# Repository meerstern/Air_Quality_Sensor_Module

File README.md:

# エアクオリティセンサ基板  
Air_Quality_Sensor_Module

## 概要 
  * ルネサスエレクトロニクス製 [室内空気質（IAQ）センサZMOD4410][1]及び[温湿度センサHS3001][2]を搭載したセンサ基板と専用変換基板です  
  * 専用変換基板を使用することで抵抗値からCO2等に変換する計算アルゴリズムをマイコン側に実装する必要がありません  
  * Arduino等のI2C通信を介して専用変換基板から容易に温湿度、CO2値等の情報を読み出すことが可能です 
  * 変換基板の[SEN]のコネクタにセンサ基板を接続し、[MPU]のコネクタにArduino等のマスタデバイスを接続してください  
  * 計算アルゴリズムはメーカ提供の学習済みニューラルネットワークを使用したファームウェア(20/10/19リリース版)を使用しています  
  * 学習済みニューラルネットワークによって従来よりもより正確にCO2値（eCO2）を推定できます  
  * 専用変換基板のLEDでIAQ(屋内空気質基準IAQ:2以下 青、2-3:青、黄、3-4:黄、4-5:黄、赤、5以上:赤)を確認できます  
  * MPU側のGrove互換コネクタに電源を供給するだけでもIAQレベルLEDで大まかな空気状態を確認することが可能です  
  * 専用変換基板の読み出し方法はサンプルプログラム(Arduino、[USBシリアルI2C変換基板][3]を使用したNode-Red)を参照してください  
  * 専用変換基板から読み出せる値は下記の通りです  
  * 専用変換基板の値は浮動小数点から10倍もしくは100倍した値を16bit符号無データ(温度のみ符号有)に変換しています  
  * センサ基板と専用変換基板、Grove互換ケーブル1本を同梱しています  
  * お手持ちの機器と変換基板を接続するGroveケーブルは同梱されていません  
  * 専用変換基板はGrove互換コネクタを搭載しており、3.3V~5V電源で駆動します  
  * I2C接続の他、Uart9600bpsでセンサデータを受信できます  

  |  項目  |  範囲  |  倍率  |
| ---- | ---- | ---- |
|  温度  |  -40-125℃  |  100倍  |
|  湿度  |  0-100%RH  |  100倍  |
|  CO2  |  400-5000ppm  |  10倍  |
|  IAQ  |  1.0-5.0  |  100倍  |
|  TVOC  |  0.01-10mg/m3  |  100倍  |
|  EtOH  |  0.01-655ppm*1  |  100倍  |
|  LogRcda  |  -  |  100倍  |      
 
 *1 専用変換基板上での制約で最大1000ppm→655ppmとなっています  
    
 ドイツ環境庁（UBA）の屋内空気質（IAQ）基準
 
  |  IAQ  |  レベル  |  LED  |
| ---- | ---- | ---- |
|  <2  |  非常に良い  |  青  |
|  2~3  |  良い  |  青と黄  |
|  3~4  |  中間  |  黄  |
|  4~5  |  悪い  |  黄と赤  |
|  5~  |  非常に悪い | 赤 |

## 注意 
 * 本センサはMOX(Metal Oxide)式のCO2センサのため、空気中の有機物から間接的にCO2に換算します。厳密なCO2計測には向きません  
 * 安定した測定をするために人通りや気流の変化が少ない場所に設置して使用してください  
 * キャリブレーション後にCO2値が安定するまで約0.5~1時間程度要します  
 * IAQは総合的な空気質の指標のため、CO2値が低くても他の有機物が多い場合に高くなります  
 * [SEN]コネクタと[MPU]コネクタの接続間違いに注意してください  
 * 電源投入後、2~3分はキャリブレーションのため、温湿度以外の値は未定で、全LEDが点灯します  
 * 専用変換基板は約2秒周期で各センサの値を取得します(データ更新時にLEDが点滅します)  
 * ZMOD4401はヒータを内蔵するため、電流を確保できる電源を使用してください(最大10mA)  
 * 専用変換基板は5V対応しておりますが、センサ基板は3.3V専用です  
 * ZMOD4410に直接アクセスして使用する場合はルネサスエレクトロニクス社にファームウェアの取得申請が必要です(法人・研究向け)  
 * ルネサスエレクトロニクス社の計算アルゴリズムは*.libもしくは*.aファイルのバイナリ形式で提供されます  
 * 告知なしに仕様を変更する場合があります    

## 参考
 * 第三者機関による[CO2センサ性能評価レポート(PDF,英語のみ)][4]  
 レポートでは他のセンサよりもZMOD4410が実際のCO2濃度に最も近い相関を示すことが報告されています  

## 販売サイト
  * [スイッチサイエンス][5]

[1]: https://www.idt.com/jp/ja/products/sensor-products/gas-sensors/zmod4410-indoor-air-quality-sensor-platform
[2]: https://www.idt.com/us/ja/products/sensor-products/humidity-sensors/hs3001-high-performance-relative-humidity-and-temperature-sensor
[3]: https://github.com/meerstern/USBSerial_I2C_Converter
[4]: https://www.renesas.com/jp/ja/document/rep/ksi-report-algorithm-evaluation-eco2-tracking?language=en
[5]: https://www.switch-science.com/products/6775

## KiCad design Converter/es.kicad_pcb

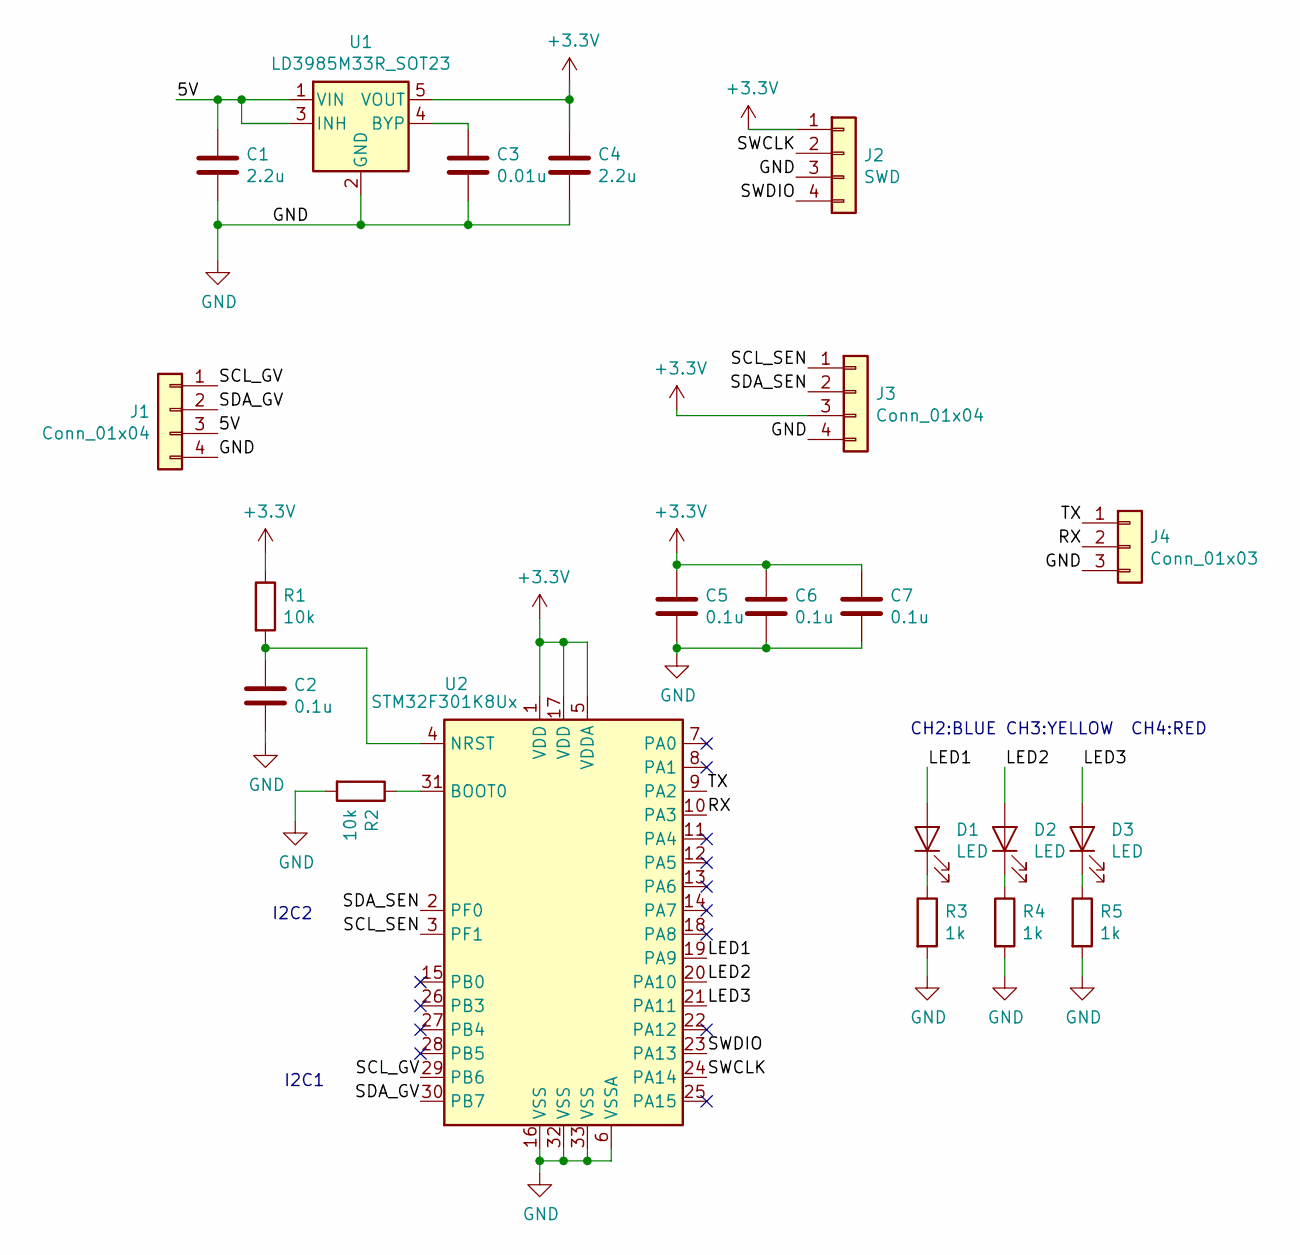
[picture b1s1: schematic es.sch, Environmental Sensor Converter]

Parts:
C1, C4: 2.2u; C_0603_1608Metric
C2, C5, C6, C7: 0.1u; C_0603_1608Metric
C3: 0.01u; C_0603_1608Metric
D1, D2, D3: LED; D_0603_1608Metric
J1, J3: Conn_01x04; GROVE
J2: SWD; PinHeader_1x04_P2.54mm_Vertical
J4: Conn_01x03; PinHeader_1x03_P2.54mm_Vertical
R1, R2: 10k; R_0603_1608Metric
R3, R4, R5: 1k; R_0603_1608Metric
U1: LD3985M33R_SOT23; SOT-23-5
U2: STM32F301K8Ux; QFN-32-1EP_5x5mm_P0.5mm_EP3.45x3.45mm

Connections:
+3V3: C4.1, C5.1, C6.1, C7.1, J2.1, J3.3, R1.1, U1.5 (VOUT), U2.1 (VDD), U2.5 (VDDA), U2.17 (VDD)
/5V: C1.1, J1.3, U1.1 (VIN), U1.3 (INH)
/LED1: D1.2 (A), U2.19 (PA9)
/LED2: D2.2 (A), U2.20 (PA10)
/LED3: D3.2 (A), U2.21 (PA11)
/RX: J4.2, U2.10 (PA3)
/SCL_GV: J1.1, U2.29 (PB6)
/SCL_SEN: J3.1, U2.3 (PF1)
/SDA_GV: J1.2, U2.30 (PB7)
/SDA_SEN: J3.2, U2.2 (PF0)
/SWCLK: J2.2, U2.24 (PA14)
/SWDIO: J2.4, U2.23 (PA13)
/TX: J4.1, U2.9 (PA2)
GND: C1.2, C2.2, C3.2, C4.2, C5.2, C6.2, C7.2, J1.4, J2.3, J3.4, J4.3, R2.2, R3.2, R4.2, R5.2, U1.2 (GND), U2.6 (VSSA), U2.16 (VSS), U2.32 (VSS), U2.33 (VSS)
unnamed: C2.1, R1.2, U2.4 (NRST)
unnamed: C3.1, U1.4 (BYP)
unnamed: D1.1 (K), R3.1
unnamed: D2.1 (K), R4.1
unnamed: D3.1 (K), R5.1
unnamed: R2.1, U2.31 (BOOT0)

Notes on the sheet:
I2C2
I2C1
CH2:BLUE
CH3:YELLOW
CH4:RED

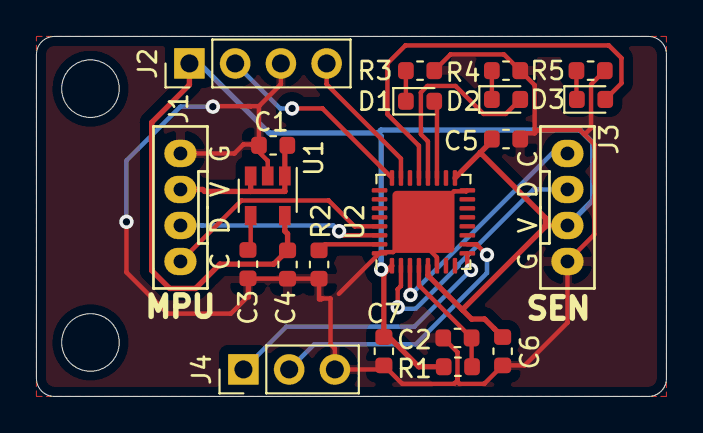
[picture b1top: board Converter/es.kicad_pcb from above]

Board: 2 copper layers, 35.0 x 20.0 mm, 23 parts (0 on the bottom side), 20 nets.

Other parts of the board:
REF1, REF2: MountingHole_3.2mm_M3

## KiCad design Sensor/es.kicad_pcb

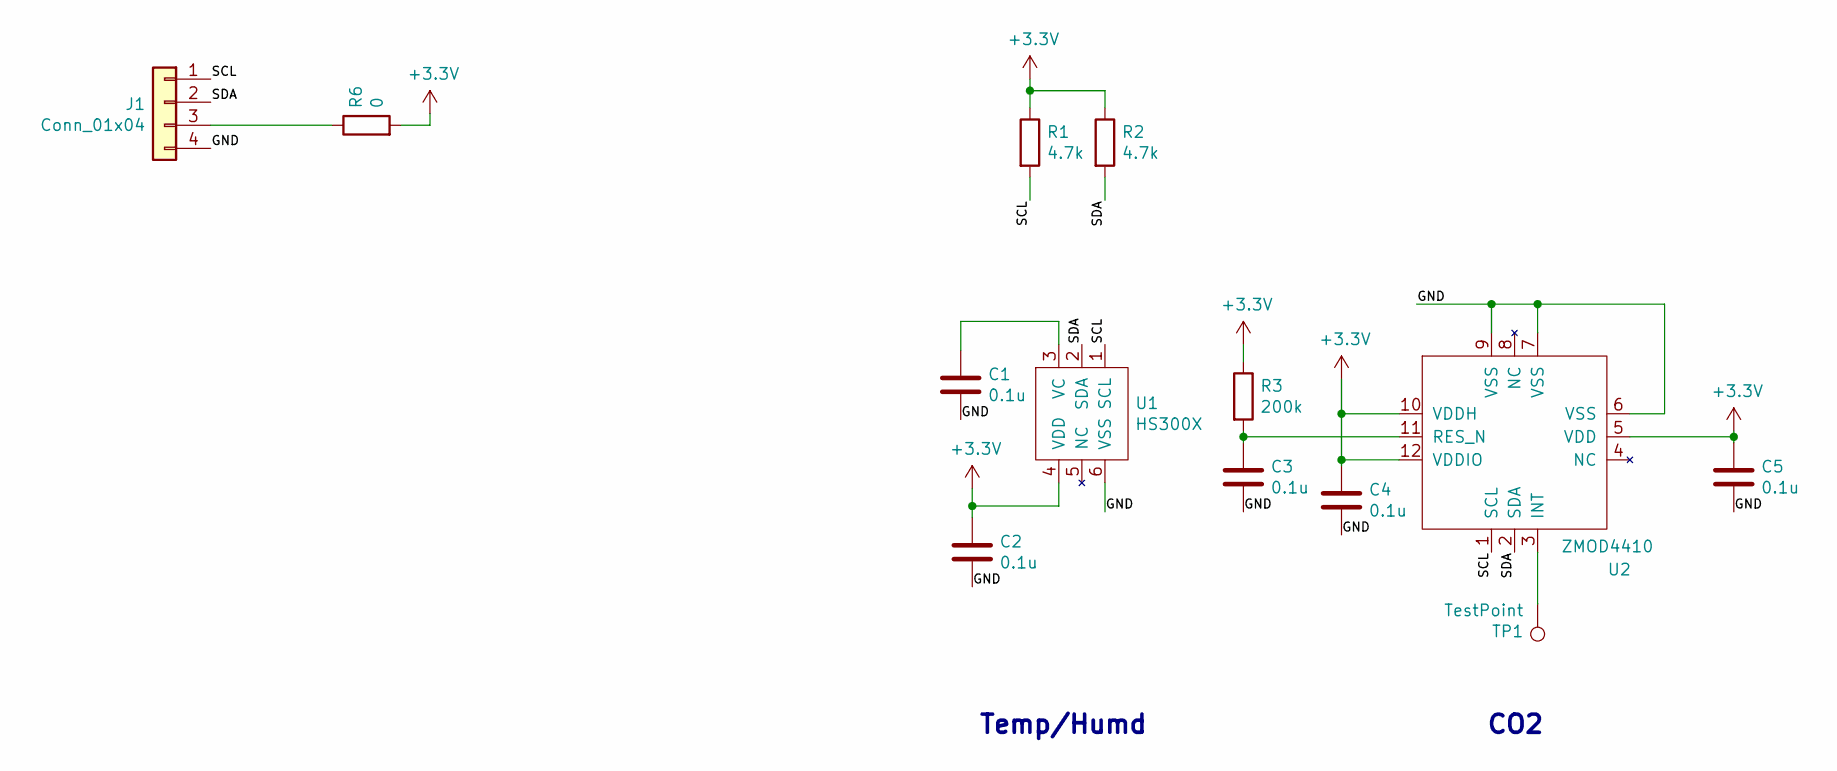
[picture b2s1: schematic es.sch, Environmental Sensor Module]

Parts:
C1, C2, C3, C4, C5: 0.1u; C_0603_1608Metric
J1: Conn_01x04; GROVE
R1, R2: 4.7k; R_0603_1608Metric
R3: 200k; R_0603_1608Metric
R6: 0; R_0603_1608Metric
TP1: TestPoint; TestPoint_THTPad_D1.0mm_Drill0.5mm
U1: HS300X
U2: ZMOD4410

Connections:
+3V3: C2.1, C4.1, C5.1, R1.1, R2.1, R3.1, R6.2, U1.4 (VDD), U2.5 (VDD), U2.10 (VDDH), U2.12 (VDDIO)
/GND: C1.2, C2.2, C3.2, C4.2, C5.2, J1.4, U1.6 (VSS), U2.6 (VSS), U2.7 (VSS), U2.9 (VSS)
/SCL: J1.1, R1.2, U1.1 (SCL), U2.1 (SCL)
/SDA: J1.2, R2.2, U1.2 (SDA), U2.2 (SDA)
unnamed: C1.1, U1.3 (VC)
unnamed: C3.1, R3.2, U2.11 (RES_N)
unnamed: J1.3, R6.1
unnamed: TP1.1, U2.3 (INT)

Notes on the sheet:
CO2
Temp/Humd

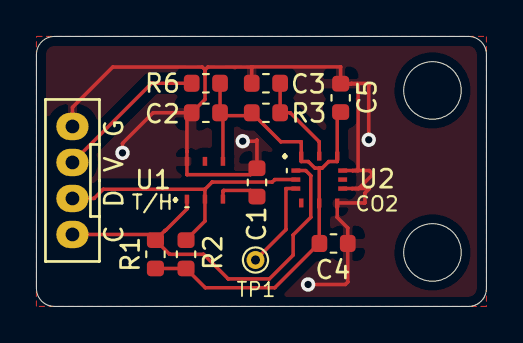
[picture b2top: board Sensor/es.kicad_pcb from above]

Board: 2 copper layers, 25.0 x 15.0 mm, 15 parts (0 on the bottom side), 8 nets.

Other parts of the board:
REF1, REF2: MountingHole_3.2mm_M3

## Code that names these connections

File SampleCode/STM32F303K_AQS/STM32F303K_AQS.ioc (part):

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Mcu.Name=STM32F303K(6-8)Tx
Mcu.Package=LQFP32
Mcu.UserName=STM32F303K8Tx
PA13.GPIOParameters=GPIO_Label
PA13.GPIO_Label=SWDIO
PA13.Mode=Serial_Wire
PA13.Signal=SYS_JTMS-SWDIO
PA14.GPIOParameters=GPIO_Label
PA14.GPIO_Label=SWCLK
PA14.Mode=Serial_Wire
PA14.Signal=SYS_JTCK-SWCLK
PA15.GPIOParameters=GPIO_Label
PA15.GPIO_Label=VCP_RX
PA15.Mode=Asynchronous
PA15.Signal=USART2_RX
PA2.GPIOParameters=GPIO_Label
PA2.GPIO_Label=VCP_TX
PA2.Mode=Asynchronous
PA2.Signal=USART2_TX
PB6.Mode=I2C
PB6.Signal=I2C1_SCL
PB7.Mode=I2C
PB7.Signal=I2C1_SDA
PF0\ /\ OSC_IN.GPIOParameters=GPIO_Label
PF0\ /\ OSC_IN.GPIO_Label=MCO
PF0\ /\ OSC_IN.Mode=HSE-External-Clock-Source
PF0\ /\ OSC_IN.Signal=RCC_OSC_IN
RCC.HSEPLLFreq_Value=8000000
RCC.HSE_VALUE=8000000
RCC.SYSCLKFreq_VALUE=64000000
RCC.SYSCLKSourceVirtual=RCC_SYSCLKSOURCE_PLLCLK
board=NUCLEO-F303K8
boardIOC=true

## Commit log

2020-11-02 add pcb files
2020-11-03 Add README
2020-11-12 Add Sample Code
2020-11-12 Add images
2020-11-23 Add sample codes for STM32F303K8 Nucleo board
2020-12-05 Add io image
2021-01-30 Add report link
2022-12-06 Add shop link
